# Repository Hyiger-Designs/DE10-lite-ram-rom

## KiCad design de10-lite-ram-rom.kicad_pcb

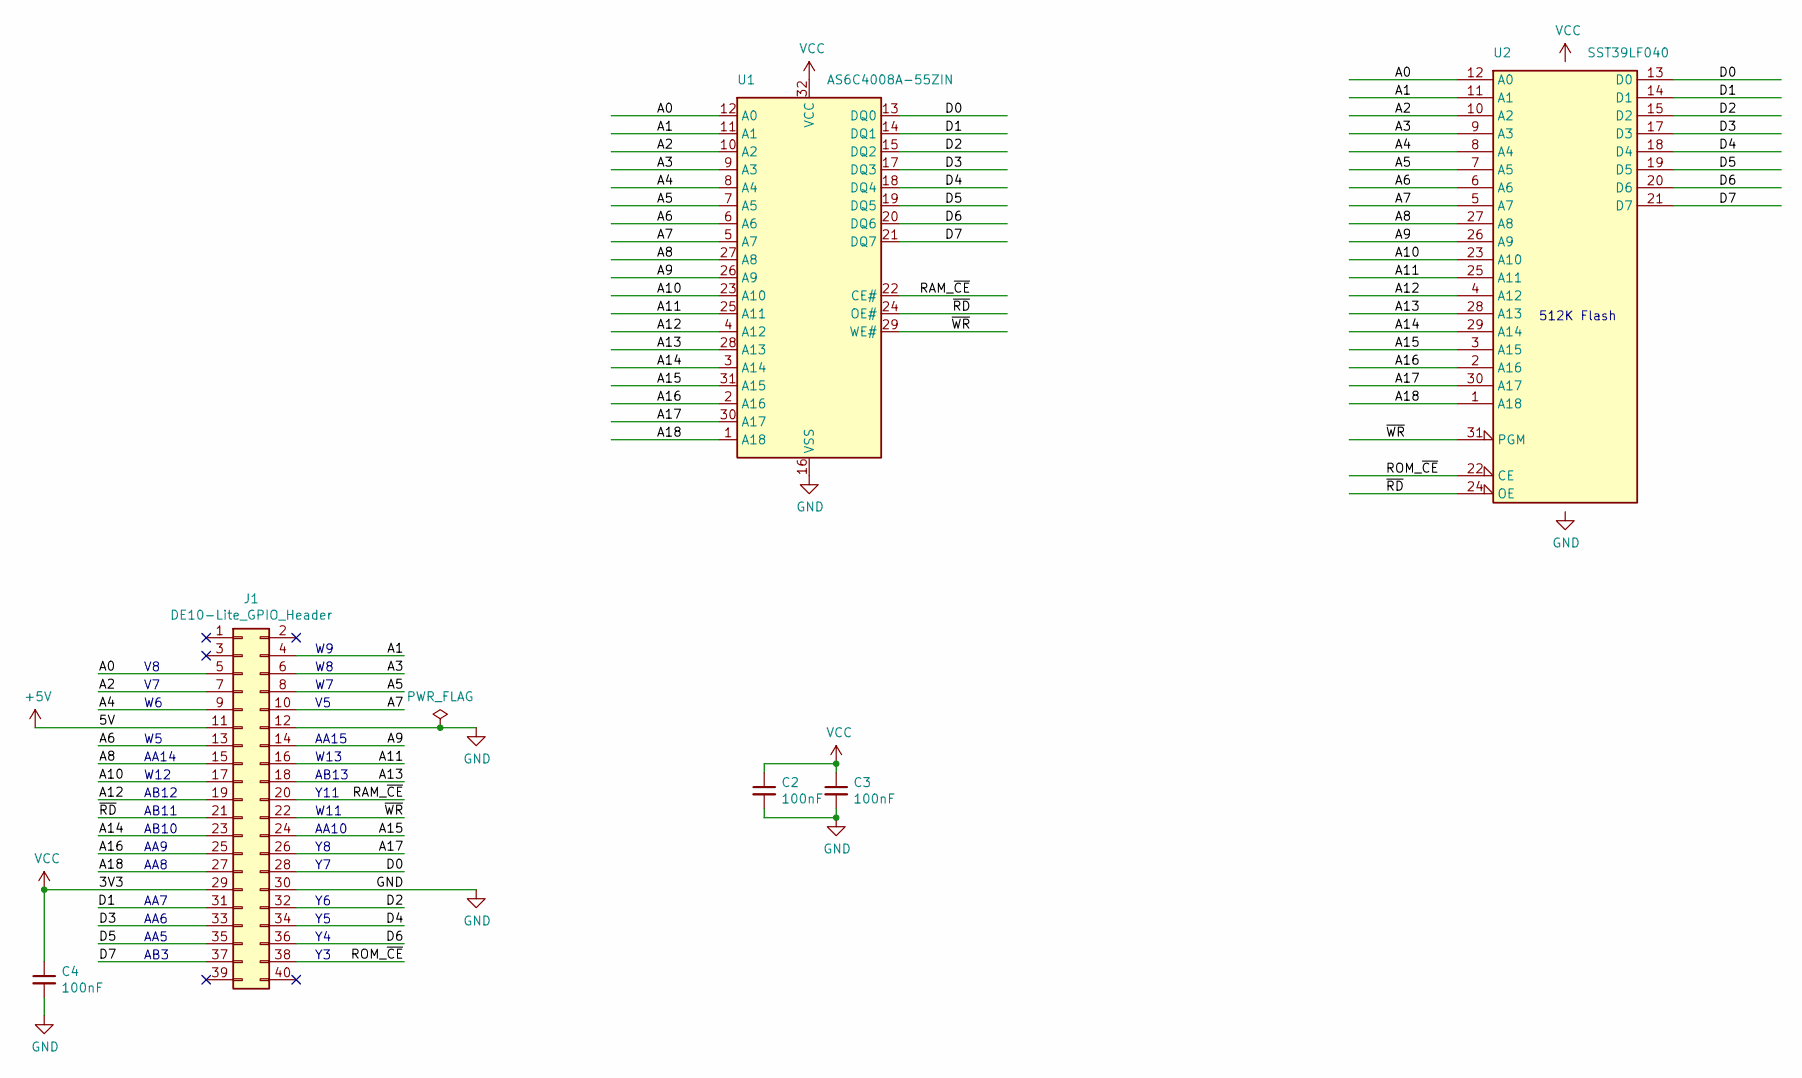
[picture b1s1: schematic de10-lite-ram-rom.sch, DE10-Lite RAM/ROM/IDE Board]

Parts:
C2, C3, C4: 100nF; C_0603_1608Metric_Pad1.05x0.95mm_HandSolder
J1: DE10-Lite_GPIO_Header; PinSocket_2x20_P2.54mm_Horizontal
U1: AS6C4008A-55ZIN; TSOP-II-32_21.0x10.2mm_P1.27mm; MPN AS6C4008A-55ZIN
U2: SST39LF040; PLCC-32_11.4x14.0mm_P1.27mm-Socket; MPN SST39LF040-55-4C-NHE-T

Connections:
+5V: J1.11 (5V)
/A0: J1.5 (Pin_V8), U1.12 (A0), U2.12 (A0)
/A1: J1.4 (Pin_W9), U1.11 (A1), U2.11 (A1)
/A2: J1.7 (Pin_V7), U1.10 (A2), U2.10 (A2)
/A3: J1.6 (Pin_W8), U1.9 (A3), U2.9 (A3)
/A4: J1.9 (Pin_W6), U1.8 (A4), U2.8 (A4)
/A5: J1.8 (Pin_W7), U1.7 (A5), U2.7 (A5)
/A6: J1.13 (Pin_W5), U1.6 (A6), U2.6 (A6)
/A7: J1.10 (Pin_V5), U1.5 (A7), U2.5 (A7)
/A8: J1.15 (Pin_AA14), U1.27 (A8), U2.27 (A8)
/A9: J1.14 (Pin_AA15), U1.26 (A9), U2.26 (A9)
/A10: J1.17 (Pin_W12), U1.23 (A10), U2.23 (A10)
/A11: J1.16 (Pin_W13), U1.25 (A11), U2.25 (A11)
/A12: J1.19 (Pin_AB12), U1.4 (A12), U2.4 (A12)
/A13: J1.18 (Pin_AB13), U1.28 (A13), U2.28 (A13)
/A14: J1.23 (Pin_AB10), U1.3 (A14), U2.29 (A14)
/A15: J1.24 (Pin_AA10), U1.31 (A15), U2.3 (A15)
/A16: J1.25 (Pin_AA9), U1.2 (A16), U2.2 (A16)
/A17: J1.26 (Pin_Y8), U1.30 (A17), U2.30 (A17)
/A18: J1.27 (Pin_AA8), U1.1 (A18), U2.1 (A18)
/D0: J1.28 (Pin_Y7), U1.13 (DQ0), U2.13 (D0)
/D1: J1.31 (Pin_AA7), U1.14 (DQ1), U2.14 (D1)
/D2: J1.32 (Pin_Y6), U1.15 (DQ2), U2.15 (D2)
/D3: J1.33 (Pin_AA6), U1.17 (DQ3), U2.17 (D3)
/D4: J1.34 (Pin_Y5), U1.18 (DQ4), U2.18 (D4)
/D5: J1.35 (Pin_AA5), U1.19 (DQ5), U2.19 (D5)
/D6: J1.36 (Pin_Y4), U1.20 (DQ6), U2.20 (D6)
/D7: J1.37 (Pin_AB3), U1.21 (DQ7), U2.21 (D7)
/RAM_~CE: J1.20 (Pin_Y11), U1.22 (CE#)
/ROM_~CE: J1.38 (Pin_Y3), U2.22 (CE)
/~RD: J1.21 (Pin_AB11), U1.24 (OE#), U2.24 (OE)
/~WR: J1.22 (Pin_W11), U1.29 (WE#), U2.31 (PGM)
GND: C2.2, C3.2, C4.2, J1.12 (GND), J1.30 (GND), U1.16 (VSS), U2.16 (GND)
VCC: C2.1, C3.1, C4.1, J1.29 (VCC), U1.32 (VCC), U2.32 (VCC)

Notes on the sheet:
512K Flash
AA15
W13
AB13
Y11
W11
AA10
AB3
AA5
AA6
AA7
AA8
AA9
AB10
AB11
AB12
W12
AA14

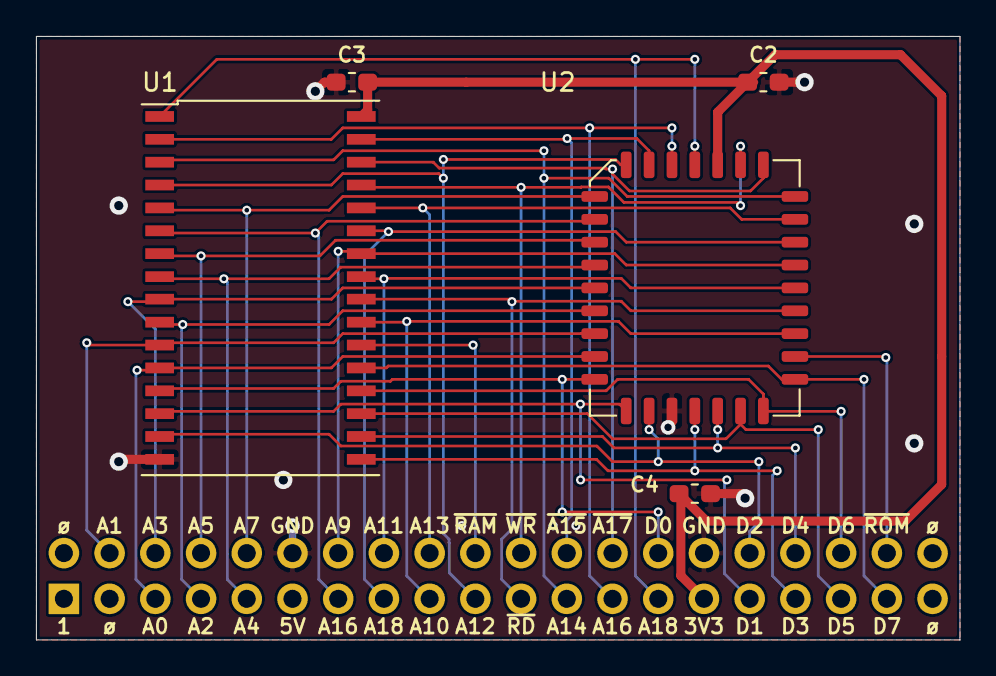
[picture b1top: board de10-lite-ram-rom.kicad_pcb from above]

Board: 2 copper layers, 51.3 x 33.5 mm, 6 parts (0 on the bottom side), 33 nets.

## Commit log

2020-04-23 Initial Version
2020-04-24 Final version
2020-04-25 removed pullups
